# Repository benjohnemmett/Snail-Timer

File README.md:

# Snail-Timer
A simple countdown timer based on an ATMega328p driving a string of WS2812 LED lights.

Blog post https://notes.benjemmett.com/archives/302

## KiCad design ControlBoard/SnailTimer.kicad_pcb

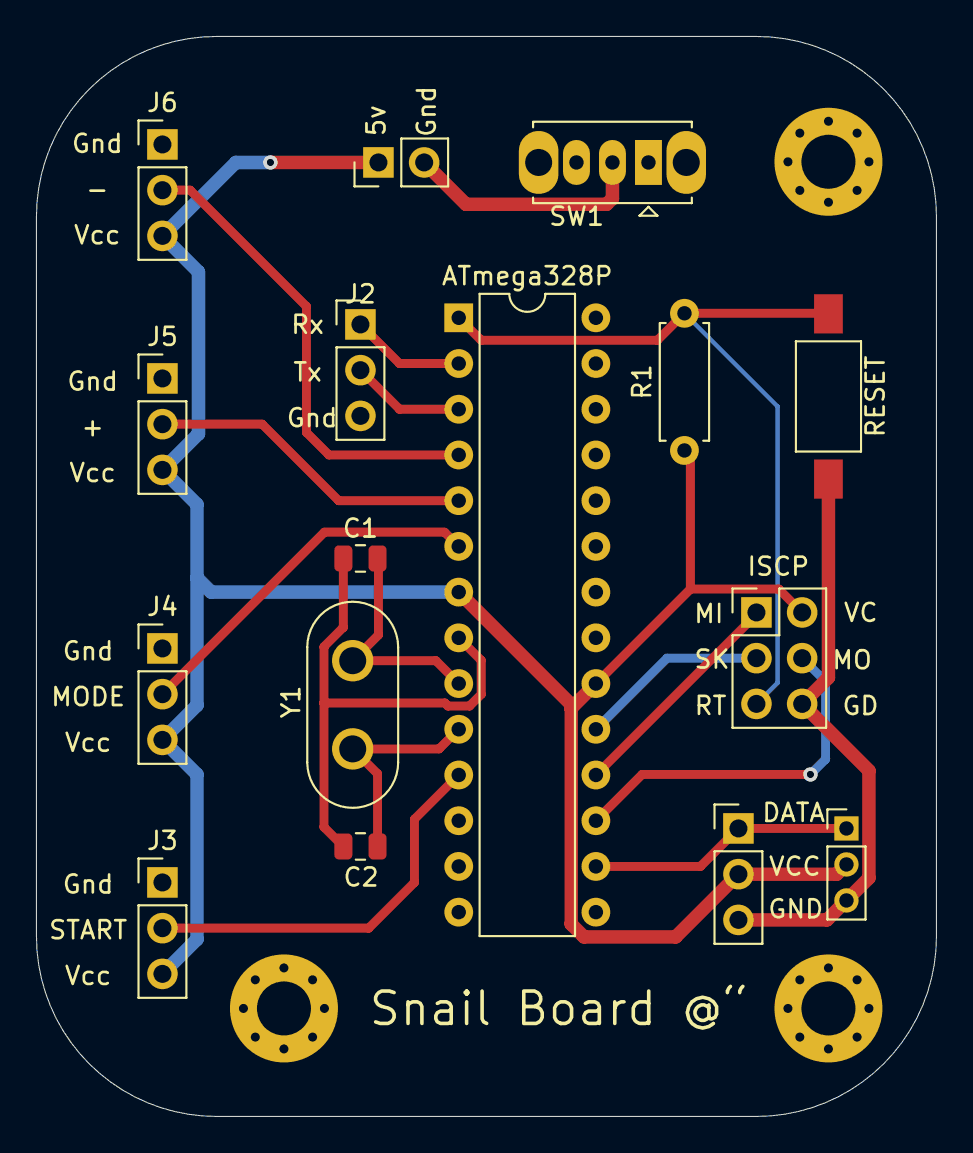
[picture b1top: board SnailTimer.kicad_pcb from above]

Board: 2 copper layers, 50.0 x 60.0 mm, 16 parts (0 on the bottom side), 16 nets.

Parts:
5v: Battery_Cell; PinHeader_1x02_P2.54mm_Vertical
ATmega328P: ATmega328-PU; DIP-28_W7.62mm
C1, C2: 22pF; C_0805_2012Metric
DATA: RGB_BIG; PinHeader_1x03_P2.54mm_Vertical
ISCP: ICSP; PinHeader_2x03_P2.54mm_Vertical
J2: SERIAL; PinHeader_1x03_P2.54mm_Vertical
J3: START; PinHeader_1x03_P2.54mm_Vertical
J4: MODE; PinHeader_1x03_P2.54mm_Vertical
J5: +; PinHeader_1x03_P2.54mm_Vertical
J6: -; PinHeader_1x03_P2.54mm_Vertical
J8: RGB_SMALL; PinHeader_1x03_P2.00mm_Vertical
R1: R; R_Axial_DIN0207_L6.3mm_D2.5mm_P7.62mm_Horizontal
RESET: RESET; SW_SPST_FSMSM
SW1: SW_SPDT; SW_Slide_1P2T_CK_OS102011MS2Q
Y1: Crystal; Crystal_HC50_Vertical

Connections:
/MINUS_BUTTON_IN: ATmega328P.4, J6.2
/MISO: ATmega328P.18, ISCP.1
/MODE_BUTTON_IN: ATmega328P.6, J4.2
/MOSI: ATmega328P.17, ISCP.4
/PLUS_BUTTON_IN: ATmega328P.5, J5.2
/RGB_DATA: ATmega328P.16, DATA.1, J8.1
/RST: ATmega328P.1, ISCP.5, R1.2, RESET.1
/RX: ATmega328P.2, J2.1
/SCK: ATmega328P.19, ISCP.3
/START_BUTTON_IN: ATmega328P.11, J3.2
/TX: ATmega328P.3, J2.2
GND: ATmega328P.8, ATmega328P.22, C1.1, C2.1, DATA.3, ISCP.6, J2.3, J3.1, J4.1, J5.1, J6.1, J8.3, RESET.2, SW1.1
unnamed: ATmega328P.9, C1.2, Y1.1
unnamed: ATmega328P.10, C2.2, Y1.2
unnamed: 5v.2, SW1.2
VCC: 5v.1, ATmega328P.7, ATmega328P.20, DATA.2, ISCP.2, J3.3, J4.3, J5.3, J6.3, J8.2, R1.1

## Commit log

2022-01-17 Initial commit. copied files from other project. Not tested.
2022-01-17 Added light_ws2812 submodule and cleaned up makefile.
2022-01-18 Cleaned up makefile & c code. Added timer end light routine.
2022-01-25 added timer reset button on INT0
2022-03-02 Added modes & did some cleanup.
2022-03-02 Coded handler for start button PD5/PCINT21.
2022-03-03 Added support for + & - buttons on the main mode.
2022-03-17 Refactored modes and udpated expired timer display mode.
2022-04-19 removed test code.
2022-04-19 Cleanup of SnailClock.c
2022-04-26 Adding control board hardware files.
